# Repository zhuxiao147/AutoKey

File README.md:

# 自动按键设置工具

这是一个基于Qt和C++开发的自动按键设置工具，用于与HID键盘模拟设备进行交互。

# 目录说明
- autokey_tool目录为上位机软件
- hardware目录为硬件开发目录
- software目录为使用stm32硬件实现的HID键盘模拟设备

## 功能特性

- **HID设备连接**: 支持连接指定VID和PID的HID设备（0x1234, 0x5678）
- **按键序列设置**: 支持设置复杂的按键序列
- **语法验证**: 提供按键序列语法检查功能
- **数据协议**: 实现完整的数据协议，包含长度、数据和CRC32校验

## 按键序列语法

- `"A;"`：表示按下并松开A键
- `"Ctrl+A;"`：表示按下Ctrl键和A键，松开时先松开A键再松开Ctrl键
- `"A(5);"`：表示按下并松开A键5次
- `"100ms;"`：表示等待100毫秒

### 示例
- `"A;Ctrl+A;A(5);100ms;"`：表示先按下并松开A键，然后按下Ctrl键和A键，松开时先松开A键再松开Ctrl键，接着按下并松开A键5次，最后等待100毫秒

## 支持的按键

- 字母键：A-Z
- 数字键：0-9
- 功能键：F1-F12
- 特殊键：Enter, Esc, Backspace, Tab, Space
- 修饰键：Ctrl, Shift, Alt, Win

## 构建要求

- Qt 5.12 或更高版本
- C++11 编译器
- Windows SDK（用于HID支持）

## 构建步骤

1. 安装Qt开发环境
2. 打开命令行，进入项目目录
3. 运行以下命令：
```bash
qmake AutoKeyTool.pro
make  # 或 nmake（Windows）
```

## 使用方法

1. 运行程序后，点击"连接设备"按钮连接HID设备
2. 在输入框中输入按键序列
3. 点击"检查序列"验证语法是否正确
4. 点击"发送序列"将按键序列发送到HID设备

## 数据协议

发送给HID设备的数据格式：
- **length**: 4字节（data的长度）
- **data**: 按键序列数据
- **crc32**: 4字节（data的crc32校验值）

## 注意事项

- 确保HID设备的VID和PID与程序中设置的一致（0x1234, 0x5678）
- 按键序列语法必须正确，否则无法发送
- 程序目前仅支持Windows平台的HID设备

## DEMO
https://github.com/user-attachments/assets/71d44151-b54c-440d-b502-1aa9202d03eb

## 许可证

MIT License

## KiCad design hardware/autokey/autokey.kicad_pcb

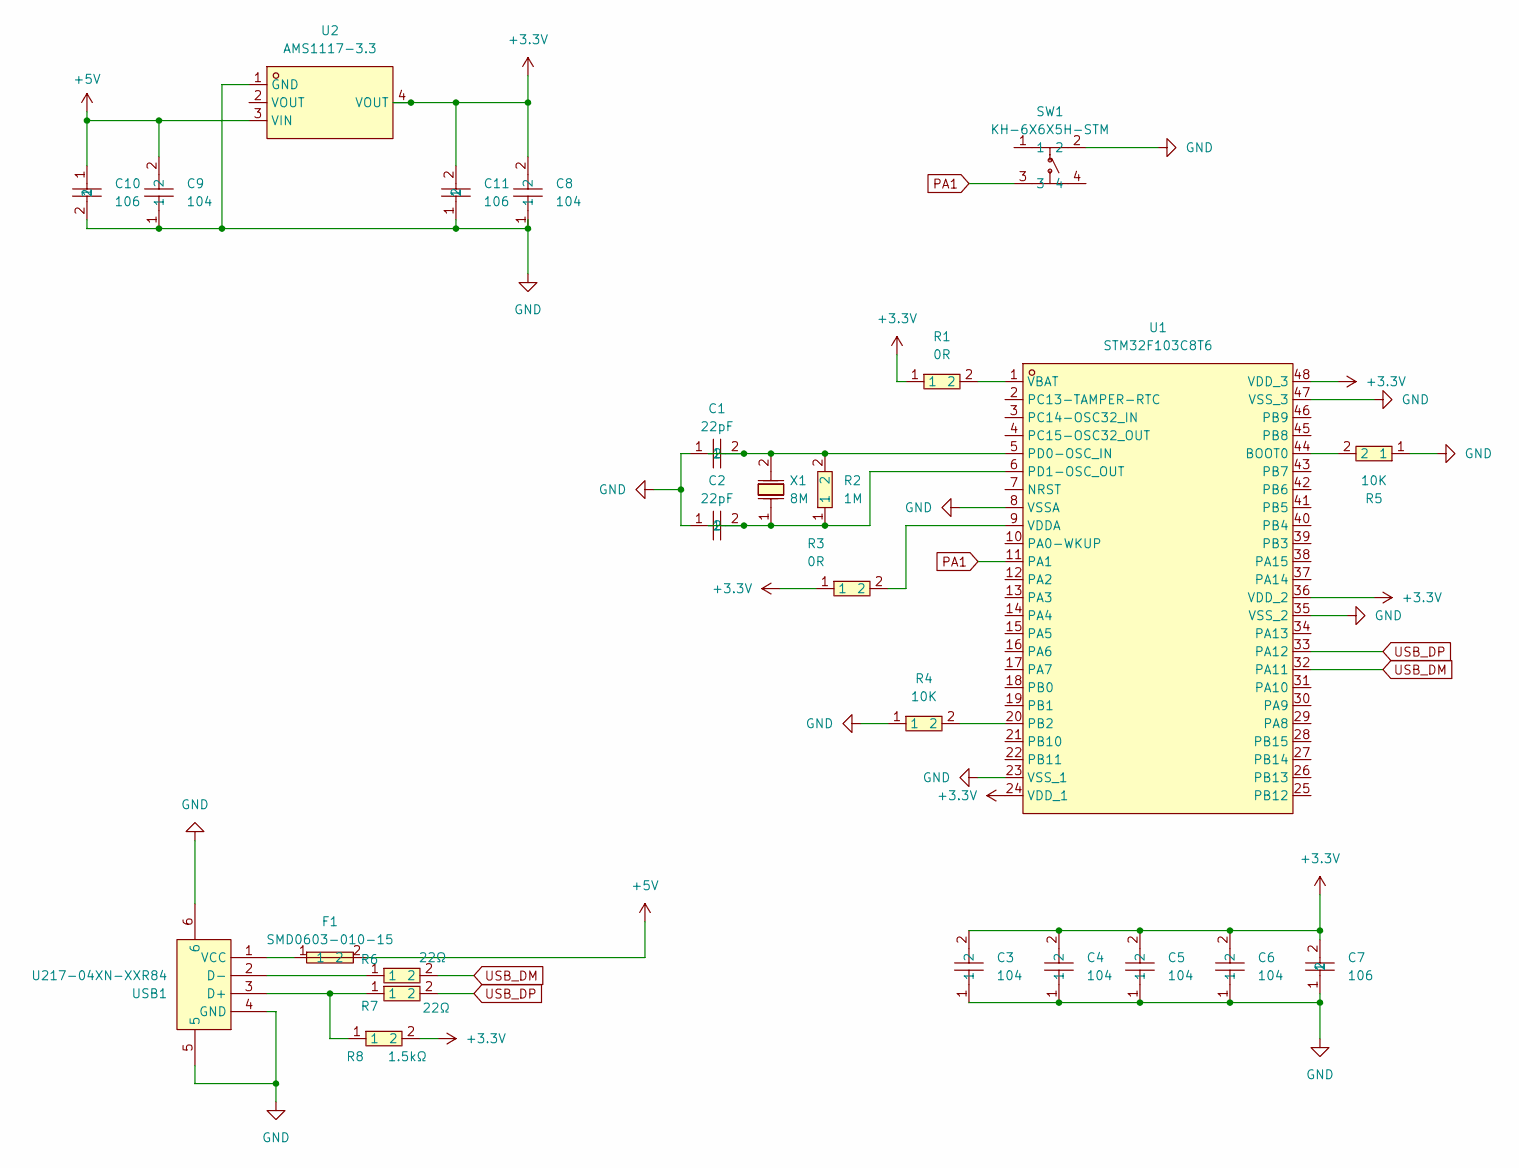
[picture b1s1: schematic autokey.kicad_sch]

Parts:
C1, C2: 22pF; C0603; LCSC Part C105620
C3, C4, C5, C6, C8, C9: 104; C0603; LCSC Part C1591
C7, C10, C11: 106; C0805; LCSC Part C1713
F1: SMD0603-010-15; F0603; LCSC Part C46640955
R1, R3: 0R; R0603; LCSC Part C21189
R2: 1M; R0603; LCSC Part C107698
R4, R5: 10K; R0603; LCSC Part C99198
R6, R7: 22Ω; R0603; LCSC Part C23345
R8: 1.5kΩ; R0603; LCSC Part C22843
SW1: KH-6X6X5H-STM; SW-SMD_4P-L6.0-W6.0-P4.50-LS9.0_H5.0; LCSC Part C2837531
U1: STM32F103C8T6; LQFP-48_L7.0-W7.0-P0.50-LS9.0-BL; LCSC Part C8734
U2: AMS1117-3.3; SOT-223-3_L6.5-W3.4-P2.30-LS7.0-BR; LCSC Part C6186
USB1: U217-04XN-XXR84; USB-A-SMD_U217-041N-4BV81; LCSC Part C319178
X1: 8M; HC-49S_L11.4-W4.8-LS12.7; LCSC Part C7528812

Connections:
+3.3V: C3.2, C4.2, C5.2, C6.2, C7.2, C8.2, C11.2, R1.1, R3.1, R8.2, U1.24 (VDD_1), U1.36 (VDD_2), U1.48 (VDD_3), U2.4 (VOUT)
+5V: C9.2, C10.1, F1.2, U2.3 (VIN)
GND: C1.1, C2.1, C3.1, C4.1, C5.1, C6.1, C7.1, C8.1, C9.1, C10.2, C11.1, R4.1, R5.1, SW1.2, U1.8 (VSSA), U1.23 (VSS_1), U1.35 (VSS_2), U1.47 (VSS_3), U2.1 (GND), USB1.4 (GND), USB1.5, USB1.6
unnamed: R5.2, U1.44 (BOOT0)
unnamed: R4.2, U1.20 (PB2)
unnamed: C1.2, R2.2, U1.5 (PD0-OSC_IN), X1.2 (OSC2)
unnamed: C2.2, R2.1, U1.6 (PD1-OSC_OUT), X1.1 (OSC1)
unnamed: R1.2, U1.1 (VBAT)
unnamed: R3.2, U1.9 (VDDA)
unnamed: R7.1, R8.1, USB1.3 (D+)
unnamed: R6.1, USB1.2 (D-)
unnamed: F1.1, USB1.1 (VCC)
PA1: SW1.3, U1.11 (PA1)
USB_DM: R6.2, U1.32 (PA11)
USB_DP: R7.2, U1.33 (PA12)

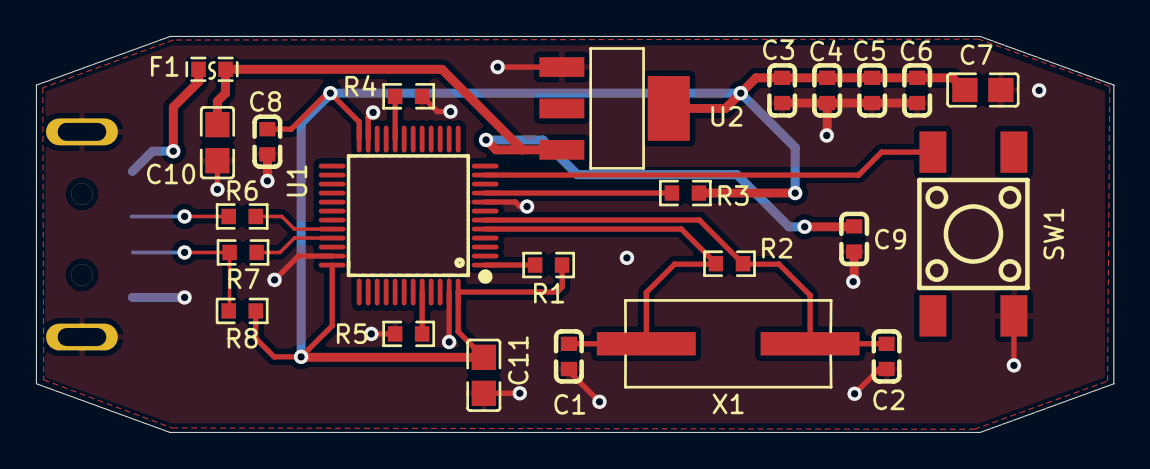
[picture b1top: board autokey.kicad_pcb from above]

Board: 2 copper layers, 59.9 x 22.0 mm, 25 parts (1 on the bottom side), 15 nets.

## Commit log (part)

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2026-01-26 feat: device can transmit with pc
2026-01-27 feat: The HID communication framework has been successfully debugged
2026-01-28 feat : autokey_tool basic finished
2026-01-28 fix: update some logic in code
2026-01-30 feat：Complete of tool data packet reassembly
2026-02-01 feat:Completion of the autokeytool sendreport section of the code
2026-02-01 feat: new data struct
2026-02-02 fix: fix the error operation that deleted autokey_web folder
2026-02-02 feat: finish receive function of sysdata.c
2026-02-03 feat:The new data protocol has been successfully debugged, but a crash bug remains unresolved.
2026-02-05 fix:fix the bug of hardfault, reason: no argument check
2026-02-07 feat:finish the beta version, but exit some transmit bug
2026-02-07 feat:enhanced the program, but exit a communication bug
2026-02-09 feat: add some code for send empty keyboard report
2026-02-10 fix : fix some code
2026-02-10 feat: Add eeprom emulation from thirdparty
2026-02-10 feat: fix all known bugs, beta version 0.0.1
2026-02-11 mod : change hareware solution
2026-02-11 Delete hardware/edalib_tool directory
    delete：delete the large file
2026-02-16 mod:modify the hardware
2026-03-13 add: finish the pcb 1.0
2026-03-13 delete: delete the tool for convert
